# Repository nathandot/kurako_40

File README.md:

# Kurako 40

## About

This project was intended to do 2 things, 1: create a board that fits original Planck-style Lo Pro cases with minor modifications, and 2: gain a better understanding of keyboard design theory by replicating one of my favorite form factors. The Kurako 40 was meant to fill a very specific niche: I needed a replacement board and I couldn't find just the board itself. I was also tiring of sales where both PCB and case must be purchased together.

Here we are a year later, spending far more on R&D than if I were to just buy an entirely new prebuilt, but where's the fun in that ;)

## Build instructions

BOM update TODO

Solder instructions TODO

Firmware build commands TODO

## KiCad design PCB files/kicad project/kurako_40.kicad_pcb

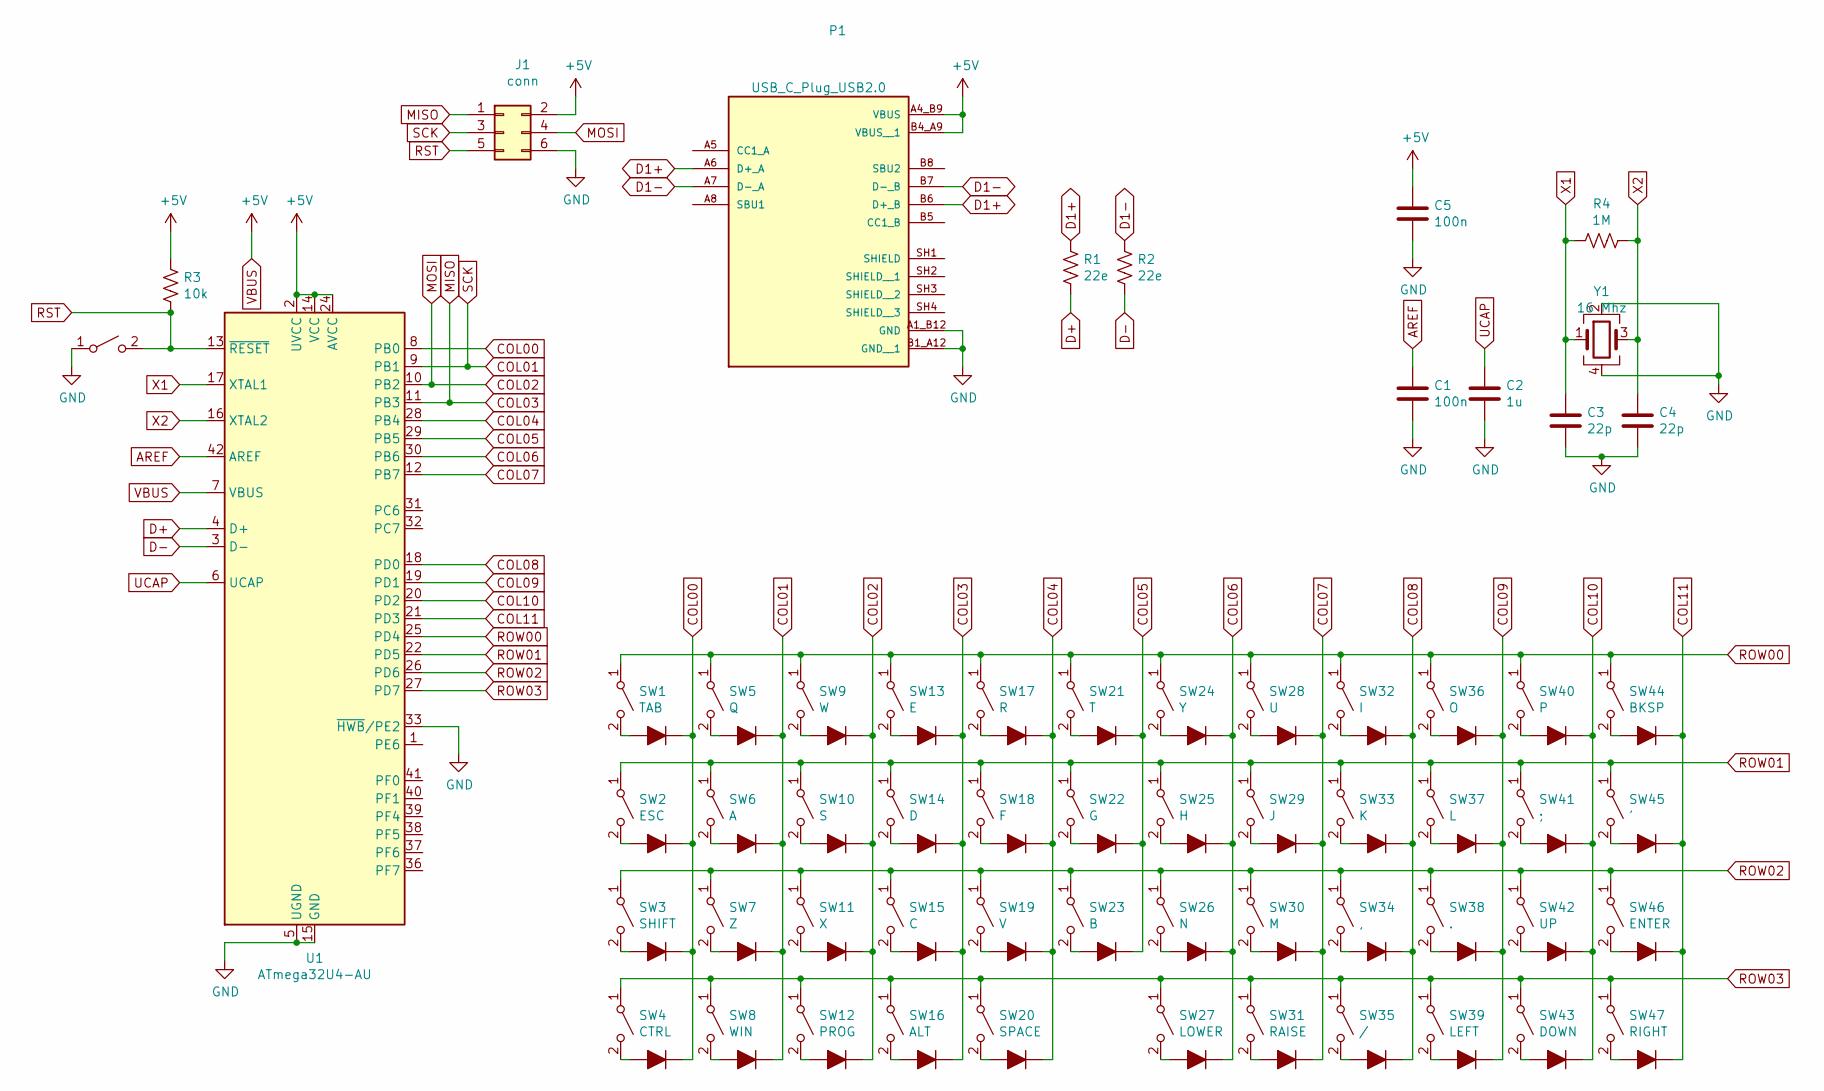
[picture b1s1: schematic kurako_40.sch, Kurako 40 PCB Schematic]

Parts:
C1, C5: 100n; C_0805_2012Metric_Pad1.15x1.40mm_HandSolder
C2: 1u; C_0805_2012Metric_Pad1.15x1.40mm_HandSolder
C3, C4: 22p; C_0805_2012Metric_Pad1.15x1.40mm_HandSolder
D1, D2, D3, D4, D5, D6, D7, D8, D9, D10, D11, D12, D13, D14, D15, D16, D17, D18, D19, D20, D21, D22, D23, D24, D25, D26, D27, D28, D29, D30, D31, D32, D33, D34, D35, D36, D37, D38, D39, D40, D41, D42, D43, D44, D45, D46, D47: D_ALT; D_MiniMELF
J1: conn; PinSocket_2x03_P2.54mm_Vertical
P1: USB_C_Plug_USB2.0; AMPHENOL_12402012E212A
R1, R2: 22e; R_0805_2012Metric_Pad1.15x1.40mm_HandSolder
R3: 10k; R_0805_2012Metric_Pad1.15x1.40mm_HandSolder
R4: 1M; R_0805_2012Metric_Pad1.15x1.40mm_HandSolder
SW1: TAB; Kailh_socket
SW2: ESC; Kailh_socket
SW3: SHIFT; Kailh_socket
SW4: CTRL; Kailh_socket
SW5: Q; Kailh_socket
SW6: A; Kailh_socket
SW7: Z; Kailh_socket
SW8: WIN; Kailh_socket
SW9: W; Kailh_socket
SW10: S; Kailh_socket
SW11: X; Kailh_socket
SW12: PROG; Kailh_socket
SW13: E; Kailh_socket
SW14: D; Kailh_socket
SW15: C; Kailh_socket
SW16: ALT; Kailh_socket
SW17: R; Kailh_socket
SW18: F; Kailh_socket
SW19: V; Kailh_socket
SW20: SPACE; Kailh_socket
SW21: T; Kailh_socket
SW22: G; Kailh_socket
SW23: B; Kailh_socket
SW24: Y; Kailh_socket
SW25: H; Kailh_socket
SW26: N; Kailh_socket
SW27: LOWER; Kailh_socket
SW28: U; Kailh_socket
SW29: J; Kailh_socket
SW30: M; Kailh_socket
SW31: RAISE; Kailh_socket
SW32: I; Kailh_socket
SW33: K; Kailh_socket
SW34: ,; Kailh_socket
SW35: /; Kailh_socket
SW36: O; Kailh_socket
SW37: L; Kailh_socket
SW38: .; Kailh_socket
SW39: LEFT; Kailh_socket
SW40: P; Kailh_socket
SW41: ;; Kailh_socket
SW42: UP; Kailh_socket
SW43: DOWN; Kailh_socket
SW44: BKSP; Kailh_socket
SW45: '; Kailh_socket
SW46: ENTER; Kailh_socket
SW47: RIGHT; Kailh_socket
SW48: SW_SPST; SW_SPST_TL3342
U1: ATmega32U4-AU; TQFP-44_10x10mm_P0.8mm
Y1: 16 Mhz; Crystal_SMD_3225-4Pin_3.2x2.5mm_HandSoldering

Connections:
AREF: C1.1, U1.42 (AREF)
COL00: D1.1 (K), D2.1 (K), D3.1 (K), D4.1 (K), U1.8 (PB0)
COL01: D5.1 (K), D6.1 (K), D7.1 (K), D8.1 (K), J1.3, U1.9 (PB1)
COL02: D9.1 (K), D10.1 (K), D11.1 (K), D12.1 (K), J1.4, U1.10 (PB2)
COL03: D13.1 (K), D14.1 (K), D15.1 (K), D16.1 (K), J1.1, U1.11 (PB3)
COL04: D17.1 (K), D18.1 (K), D19.1 (K), D20.1 (K), U1.28 (PB4)
COL05: D21.1 (K), D22.1 (K), D23.1 (K), U1.29 (PB5)
COL06: D24.1 (K), D25.1 (K), D26.1 (K), D27.1 (K), U1.30 (PB6)
COL07: D28.1 (K), D29.1 (K), D30.1 (K), D31.1 (K), U1.12 (PB7)
COL08: D32.1 (K), D33.1 (K), D34.1 (K), D35.1 (K), U1.18 (PD0)
COL09: D36.1 (K), D37.1 (K), D38.1 (K), D39.1 (K), U1.19 (PD1)
COL10: D40.1 (K), D41.1 (K), D42.1 (K), D43.1 (K), U1.20 (PD2)
COL11: D44.1 (K), D45.1 (K), D46.1 (K), D47.1 (K), U1.21 (PD3)
D1+: P1.A6 (D+_A), P1.B6 (D+_B), R1.1
D1-: P1.A7 (D-_A), P1.B7 (D-_B), R2.1
D+: R1.2, U1.4 (D+)
D-: R2.2, U1.3 (D-)
GND: C1.2, C2.2, C3.2, C4.2, C5.2, J1.6, P1.A1_B12 (GND), P1.B1_A12 (GND__1), SW48.1 (A), U1.5 (UGND), U1.15 (GND), U1.23 (GND), U1.33 (~HWB~/PE2), U1.35 (GND), U1.43 (GND), Y1.2, Y1.4
unnamed: D1.2 (A), SW1.2 (B)
unnamed: D2.2 (A), SW2.2 (B)
unnamed: D3.2 (A), SW3.2 (B)
unnamed: D4.2 (A), SW4.2 (B)
unnamed: D5.2 (A), SW5.2 (B)
unnamed: D6.2 (A), SW6.2 (B)
unnamed: D7.2 (A), SW7.2 (B)
unnamed: D8.2 (A), SW8.2 (B)
unnamed: D9.2 (A), SW9.2 (B)
unnamed: D10.2 (A), SW10.2 (B)
unnamed: D11.2 (A), SW11.2 (B)
unnamed: D12.2 (A), SW12.2 (B)
unnamed: D13.2 (A), SW13.2 (B)
unnamed: D14.2 (A), SW14.2 (B)
unnamed: D15.2 (A), SW15.2 (B)
unnamed: D16.2 (A), SW16.2 (B)
unnamed: D17.2 (A), SW17.2 (B)
unnamed: D18.2 (A), SW18.2 (B)
unnamed: D19.2 (A), SW19.2 (B)
unnamed: D20.2 (A), SW20.2 (B)
unnamed: D21.2 (A), SW21.2 (B)
unnamed: D22.2 (A), SW22.2 (B)
unnamed: D23.2 (A), SW23.2 (B)
unnamed: D24.2 (A), SW24.2 (B)
unnamed: D25.2 (A), SW25.2 (B)
unnamed: D26.2 (A), SW26.2 (B)
unnamed: D27.2 (A), SW27.2 (B)
unnamed: D28.2 (A), SW28.2 (B)
unnamed: D29.2 (A), SW29.2 (B)
unnamed: D30.2 (A), SW30.2 (B)
unnamed: D31.2 (A), SW31.2 (B)
unnamed: D32.2 (A), SW32.2 (B)
unnamed: D33.2 (A), SW33.2 (B)
unnamed: D34.2 (A), SW34.2 (B)
unnamed: D35.2 (A), SW35.2 (B)
unnamed: D36.2 (A), SW36.2 (B)
unnamed: D37.2 (A), SW37.2 (B)
unnamed: D38.2 (A), SW38.2 (B)
unnamed: D39.2 (A), SW39.2 (B)
unnamed: D40.2 (A), SW40.2 (B)
unnamed: D41.2 (A), SW41.2 (B)
unnamed: D42.2 (A), SW42.2 (B)
unnamed: D43.2 (A), SW43.2 (B)
unnamed: D44.2 (A), SW44.2 (B)
unnamed: D45.2 (A), SW45.2 (B)
unnamed: D46.2 (A), SW46.2 (B)
unnamed: D47.2 (A), SW47.2 (B)
ROW00: SW1.1 (A), SW5.1 (A), SW9.1 (A), SW13.1 (A), SW17.1 (A), SW21.1 (A), SW24.1 (A), SW28.1 (A), SW32.1 (A), SW36.1 (A), SW40.1 (A), SW44.1 (A), U1.25 (PD4)
ROW01: SW2.1 (A), SW6.1 (A), SW10.1 (A), SW14.1 (A), SW18.1 (A), SW22.1 (A), SW25.1 (A), SW29.1 (A), SW33.1 (A), SW37.1 (A), SW41.1 (A), SW45.1 (A), U1.22 (PD5)
ROW02: SW3.1 (A), SW7.1 (A), SW11.1 (A), SW15.1 (A), SW19.1 (A), SW23.1 (A), SW26.1 (A), SW30.1 (A), SW34.1 (A), SW38.1 (A), SW42.1 (A), SW46.1 (A), U1.26 (PD6)
ROW03: SW4.1 (A), SW8.1 (A), SW12.1 (A), SW16.1 (A), SW20.1 (A), SW27.1 (A), SW31.1 (A), SW35.1 (A), SW39.1 (A), SW43.1 (A), SW47.1 (A), U1.27 (PD7)
RST: J1.5, R3.2, SW48.2 (B), U1.13 (~RESET)
UCAP: C2.1, U1.6 (UCAP)
VBUS: C5.1, J1.2, P1.A4_B9 (VBUS), P1.B4_A9 (VBUS__1), R3.1, U1.2 (UVCC), U1.7 (VBUS), U1.14 (VCC), U1.24 (AVCC), U1.34 (VCC), U1.44 (AVCC)
X1: C3.1, R4.1, U1.17 (XTAL1), Y1.1
X2: C4.1, R4.2, U1.16 (XTAL2), Y1.3

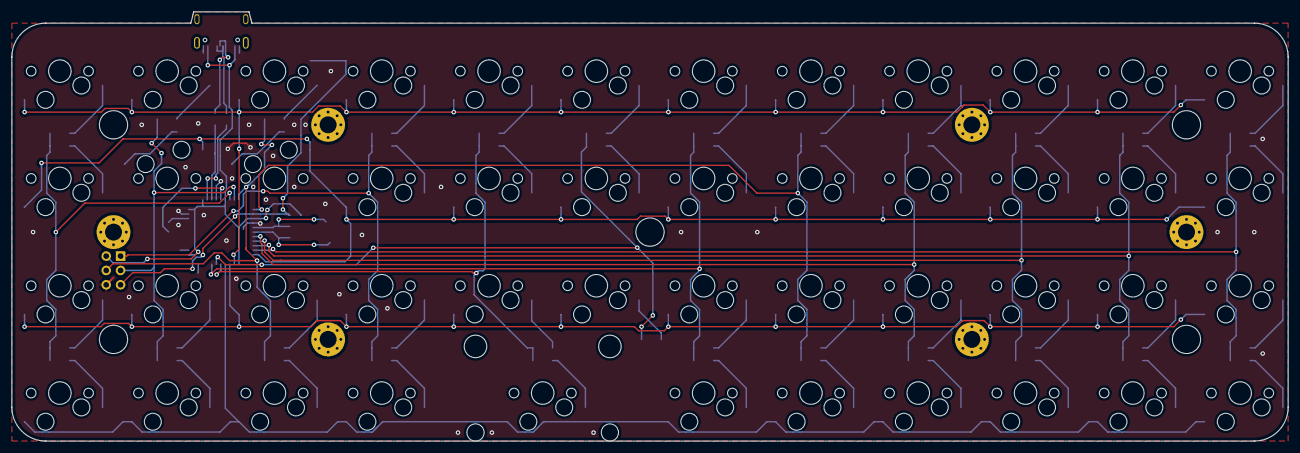
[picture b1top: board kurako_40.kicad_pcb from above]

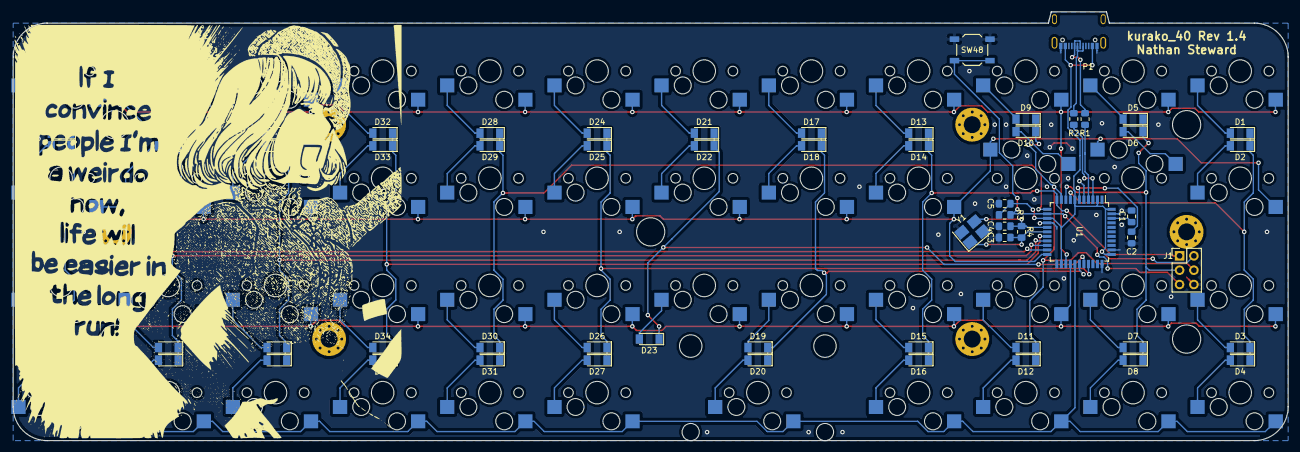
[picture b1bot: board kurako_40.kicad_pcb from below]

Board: 2 copper layers, 226.0 x 76.0 mm, 108 parts (60 on the bottom side), 74 nets.

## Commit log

2022-11-07 initial upload
    first upload, renamed, set up firmware and pcb files.
    created 10/1/21, but not officiated until 11/6/22
2022-11-07 update pcb files
    first rev ordered with this board
2022-11-07 created readme
    pictures! in a readme!
2022-11-07 bad keyswitch placements
    prior rev had bad switch placement, updated and gave the board a rev number
2022-11-14 board rev changes v1.2
    updated schematic from SOD323 diodes to SOD80 due to cost savings and ease of soldering. added ground fill on top and bottom
2022-11-29 minor board and code change
    updated usb placement to not stick out as much (-0.75mm)
    swapped diode polarity in firmware config
    corrected main board header file
2022-11-29 library updates
    included external libraries for KiCad,and updated generated gerber files
2024-03-11 usb c updates
    chose better USB connector for hand soldering
